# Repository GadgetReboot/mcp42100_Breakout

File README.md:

# mcp42100_Breakout
<br><br><BR><BR>
Dual 100k digital pot MCP42100 Breakout Board

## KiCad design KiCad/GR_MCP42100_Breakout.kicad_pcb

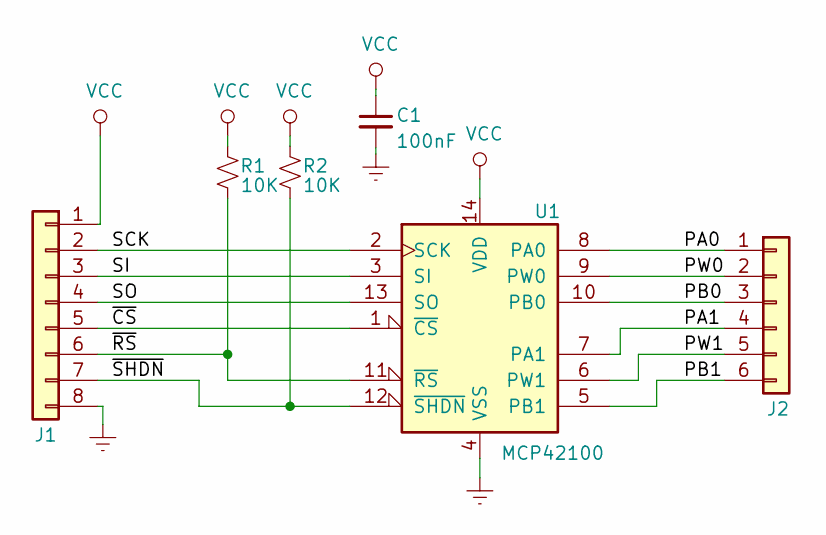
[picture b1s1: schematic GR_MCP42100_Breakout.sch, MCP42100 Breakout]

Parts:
C1: 100nF; C_0805_2012Metric_Pad1.15x1.40mm_HandSolder
J1: Conn_01x08; PinHeader_1x08_P2.54mm_Vertical
J2: Conn_01x06; PinHeader_1x06_P2.54mm_Vertical
R1, R2: 10K; R_0805_2012Metric_Pad1.15x1.40mm_HandSolder
U1: MCP42100; SOIC-14_3.9x8.7mm_P1.27mm

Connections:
/PA0: J2.1, U1.8 (PA0)
/PA1: J2.4, U1.7 (PA1)
/PB0: J2.3, U1.10 (PB0)
/PB1: J2.6, U1.5 (PB1)
/PW0: J2.2, U1.9 (PW0)
/PW1: J2.5, U1.6 (PW1)
/SCK: J1.2, U1.2 (SCK)
/SI: J1.3, U1.3 (SI)
/SO: J1.4, U1.13 (SO)
/~CS: J1.5, U1.1 (~CS)
/~RS: J1.6, R1.2, U1.11 (~RS)
/~SHDN: J1.7, R2.2, U1.12 (~SHDN)
GNDREF: C1.2, J1.8, U1.4 (VSS)
VCC: C1.1, J1.1, R1.1, R2.1, U1.14 (VDD)

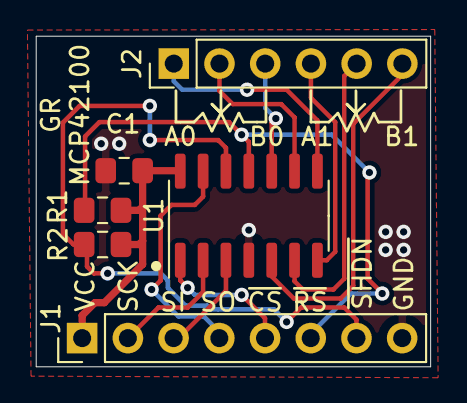
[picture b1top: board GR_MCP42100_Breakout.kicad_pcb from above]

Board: 2 copper layers, 21.9 x 18.4 mm, 6 parts (0 on the bottom side), 14 nets.
